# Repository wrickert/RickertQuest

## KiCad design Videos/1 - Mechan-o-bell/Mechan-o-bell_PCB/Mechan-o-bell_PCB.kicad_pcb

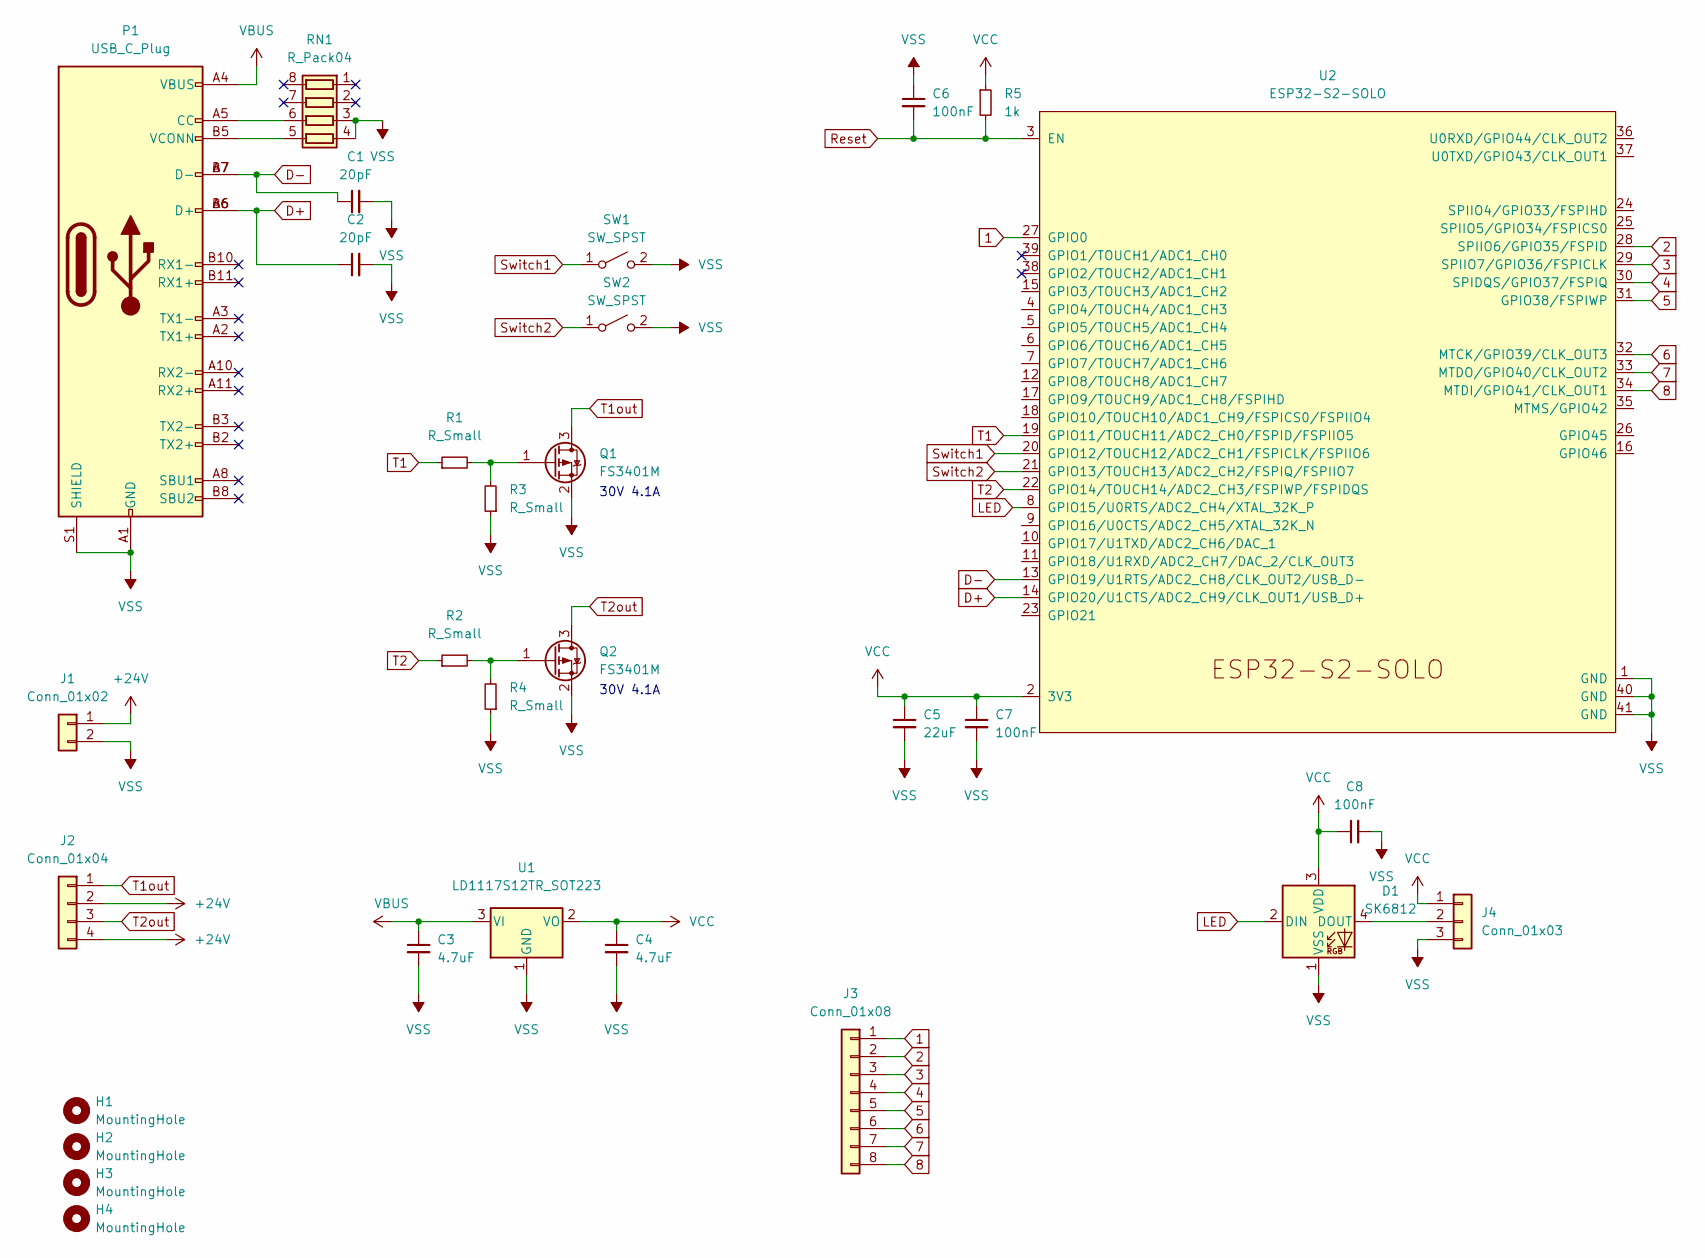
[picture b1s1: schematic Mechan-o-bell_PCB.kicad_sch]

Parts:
C1, C2: 20pF; C_0805_2012Metric
C3, C4: 4.7uF; C_0805_2012Metric
C5: 22uF; C_0805_2012Metric
C6, C7, C8: 100nF; C_0805_2012Metric
D1: SK6812; LED_SK6812_PLCC4_5.0x5.0mm_P3.2mm
H1, H2, H3, H4: MountingHole; MountingHole_4.3mm_M4
J1: Conn_01x02; TerminalBlock_Altech_AK300-2_P5.00mm
J2: Conn_01x04; TerminalBlock_Altech_AK300-4_P5.00mm
J3: Conn_01x08; PinHeader_1x08_P2.54mm_Vertical
J4: Conn_01x03; PinHeader_1x03_P2.54mm_Vertical
P1: USB_C_Plug; USB_C_Receptical-Jing
Q1, Q2: FS3401M; SOT-23
R1, R2, R3, R4: R_Small; R_0805_2012Metric
R5: 1k; R_0805_2012Metric
RN1: R_Pack04; R_Array_Concave_4x0603
SW1, SW2: SW_SPST; SW_SPST_B3SL-1002P
U1: LD1117S12TR_SOT223; SOT-223-3_TabPin2
U2: ESP32-S2-SOLO

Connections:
1: J3.1, U2.27 (GPIO0)
2: J3.2, U2.28 (SPIIO6/GPIO35/FSPID)
3: J3.3, U2.29 (SPIIO7/GPIO36/FSPICLK)
4: J3.4, U2.30 (SPIDQS/GPIO37/FSPIQ)
5: J3.5, U2.31 (GPIO38/FSPIWP)
6: J3.6, U2.32 (MTCK/GPIO39/CLK_OUT3)
7: J3.7, U2.33 (MTDO/GPIO40/CLK_OUT2)
8: J3.8, U2.34 (MTDI/GPIO41/CLK_OUT1)
+24V: J1.1, J2.2, J2.4
D+: C2.1, P1.A6 (D+), P1.B6 (D+), U2.14 (GPIO20/U1CTS/ADC2_CH9/CLK_OUT1/USB_D+)
D-: C1.1, P1.A7 (D-), P1.B7 (D-), U2.13 (GPIO19/U1RTS/ADC2_CH8/CLK_OUT2/USB_D-)
LED: D1.2 (DIN), U2.8 (GPIO15/U0RTS/ADC2_CH4/XTAL_32K_P)
unnamed: D1.4 (DOUT), J4.2
unnamed: P1.A5 (CC), RN1.6 (R3.2)
unnamed: P1.B5 (VCONN), RN1.5 (R4.2)
unnamed: Q1.1 (G), R1.2, R3.2
unnamed: Q2.1 (G), R2.2, R4.2
Reset: C6.2, R5.2, U2.3 (EN)
Switch1: SW1.1 (A), U2.20 (GPIO12/TOUCH12/ADC2_CH1/FSPICLK/FSPIIO6)
Switch2: SW2.1 (A), U2.21 (GPIO13/TOUCH13/ADC2_CH2/FSPIQ/FSPIIO7)
T1: R1.1, U2.19 (GPIO11/TOUCH11/ADC2_CH0/FSPID/FSPIIO5)
T1out: J2.1, Q1.3 (D)
T2: R2.1, U2.22 (GPIO14/TOUCH14/ADC2_CH3/FSPIWP/FSPIDQS)
T2out: J2.3, Q2.3 (D)
VBUS: C3.1, P1.A4 (VBUS), P1.A9 (VBUS), P1.B4 (VBUS), P1.B9 (VBUS), U1.3 (VI)
VCC: C4.1, C5.1, C7.1, C8.1, D1.3 (VDD), J4.1, R5.1, U1.2 (VO), U2.2 (3V3)
VSS: C1.2, C2.2, C3.2, C4.2, C5.2, C6.1, C7.2, C8.2, D1.1 (VSS), J1.2, J4.3, P1.A1 (GND), P1.A12 (GND), P1.B1 (GND), P1.B12 (GND), P1.S1 (SHIELD), Q1.2 (S), Q2.2 (S), R3.1, R4.1, RN1.3 (R3.1), RN1.4 (R4.1), SW1.2 (B), SW2.2 (B), U1.1 (GND), U2.1 (GND), U2.40 (GND), U2.41 (GND)

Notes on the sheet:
30V 4.1A

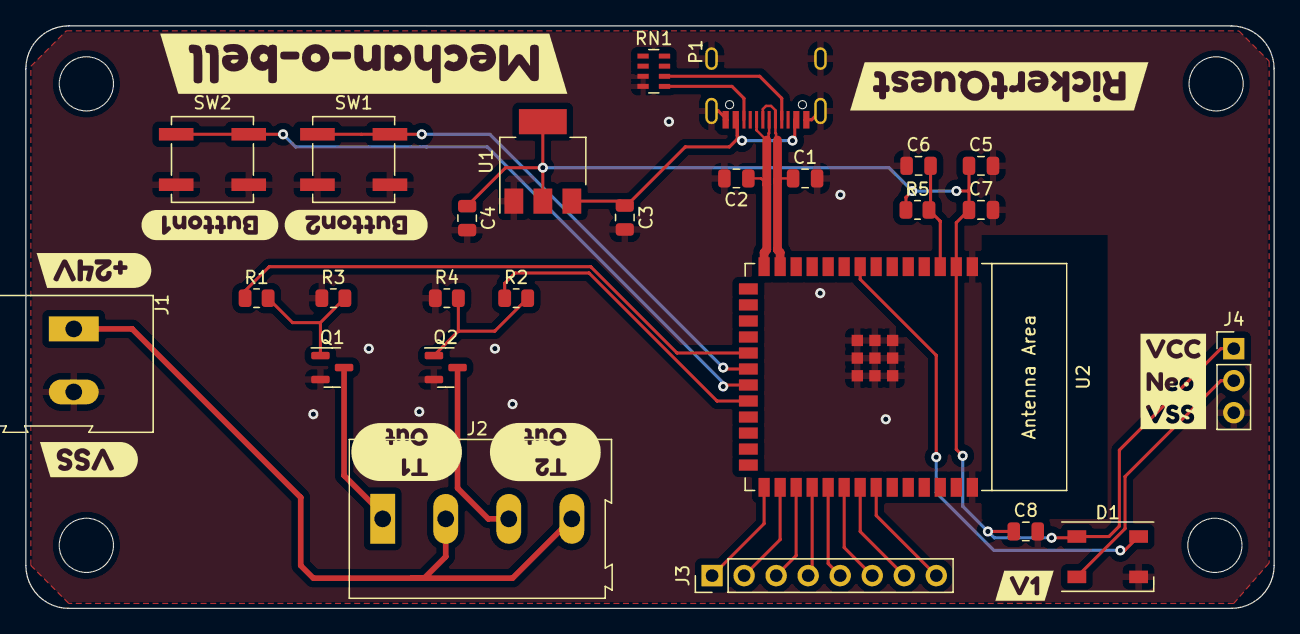
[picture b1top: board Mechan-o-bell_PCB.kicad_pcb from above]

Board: 2 copper layers, 99.0 x 46.2 mm, 41 parts (1 on the bottom side), 27 nets.

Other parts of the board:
kibuzzard-6314DFBD: G***; kibuzzard-6314DFBD
kibuzzard-6314DFC9: G***; kibuzzard-6314DFC9
kibuzzard-6314DFCF: G***; kibuzzard-6314DFCF
kibuzzard-6314DFD4: G***; kibuzzard-6314DFD4
kibuzzard-6314DFD9: G***; kibuzzard-6314DFD9
kibuzzard-6314DFE1: G***; kibuzzard-6314DFE1
kibuzzard-6314DFF6: G***; kibuzzard-6314DFF6
kibuzzard-6314E01A: G***; kibuzzard-6314E01A
kibuzzard-6314E009: G***; kibuzzard-6314E009
kibuzzard-6314E025: G***; kibuzzard-6314E025
kibuzzard-6314E056: G***; kibuzzard-6314E056
